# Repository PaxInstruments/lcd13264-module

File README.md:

# Pax Instruments
# LCD13264-module

[Pax Instruments Template Module](<link to store page>)

## Overview
The Pax Instruments LCD13264-module is a breakout shield for the LCD23164 graphic LCD.

## Repository Contents
- __Datasheets__ - Datasheets for relevant components and parts
- __Electronics__ - All PCB and schematic design files
- __Enclosure__ - Enclosure 3D design files
- __Firmware__ - Firmware, libraries, and examples
- __Production__ - Manufacturing resources
- __Resources__ - Other resources

## Product Versions

## License Information
```
Place the license statement here
```

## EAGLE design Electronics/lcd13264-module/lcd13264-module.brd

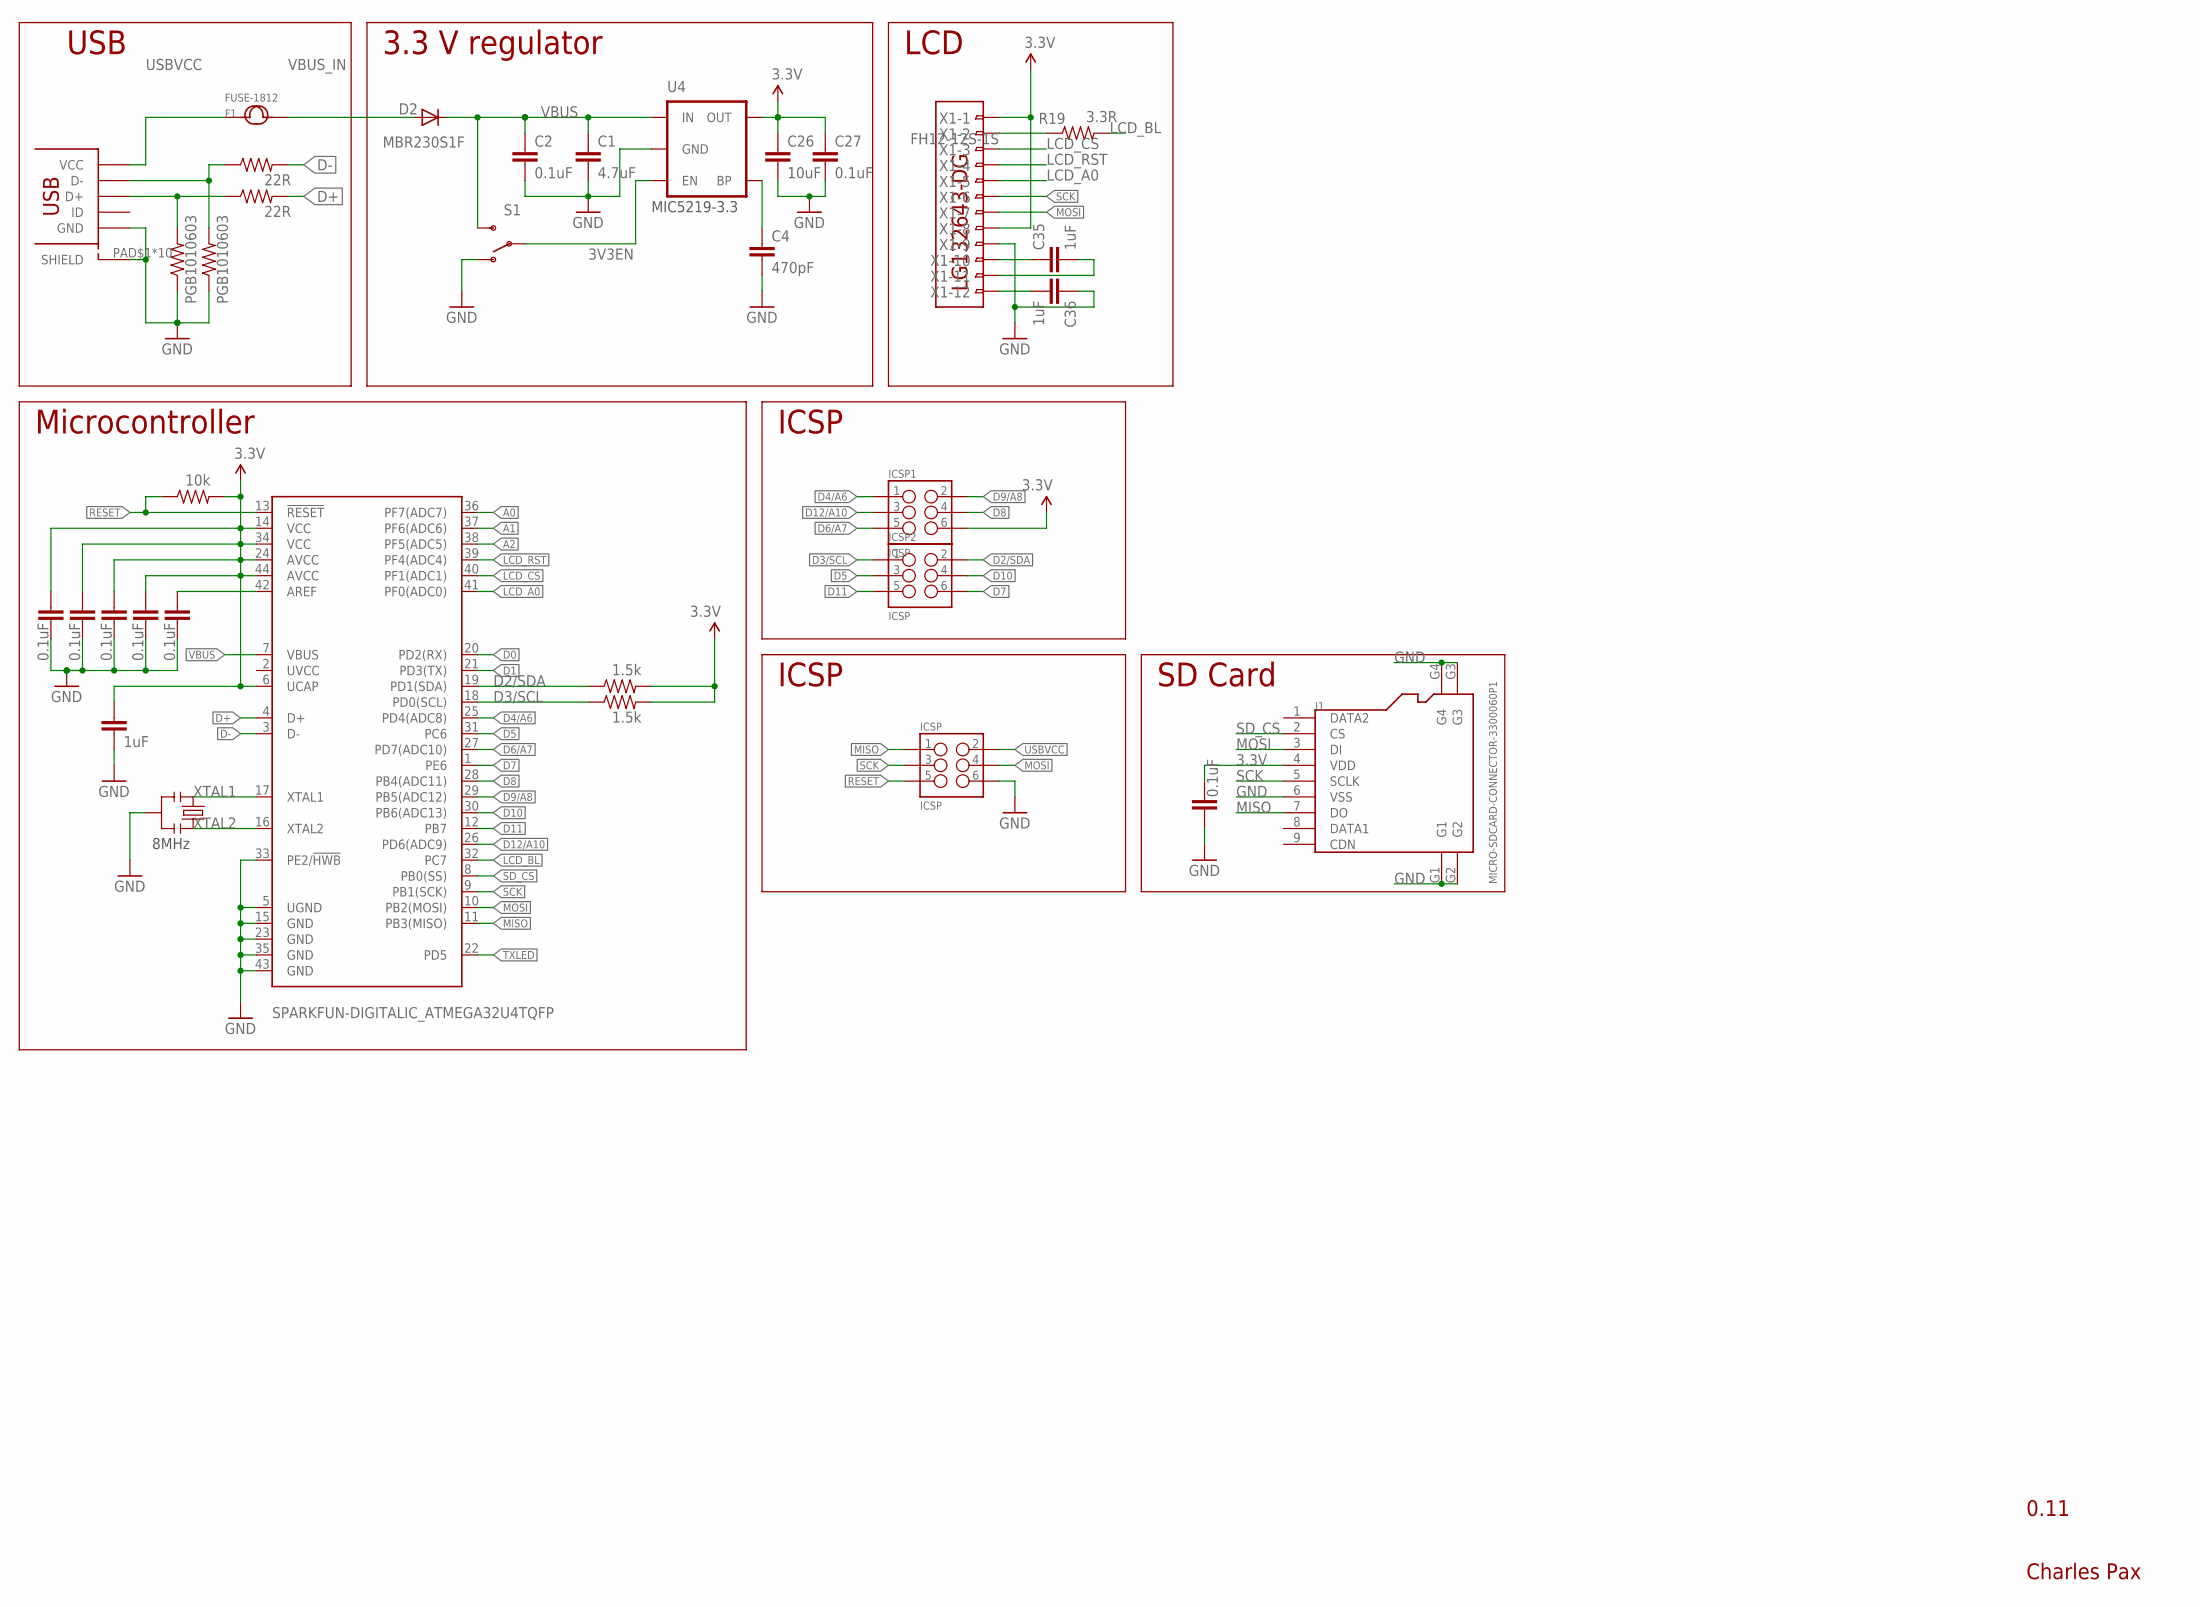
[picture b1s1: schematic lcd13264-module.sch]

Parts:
C1: 4.7uF; SPARKFUN-CAPACITORS_0603-CAP; MPN GRM188R60J475KE19D
C2, C3, C5, C21, C27, C32, C33, C34: 0.1uF; SPARKFUN-CAPACITORS_0603-CAP; MPN CL10B104KO8NNNC
C4: 470pF; SPARKFUN-CAPACITORS_0603-CAP; MPN C1608X5R1A474K080AA
C19, C35, C36: 1uF; SPARKFUN-CAPACITORS_0603-CAP; MPN LMK107B7105KA-T
C26: 10uF; SPARKFUN-CAPACITORS_0603-CAP; MPN JMK107ABJ106MAHT
D2: MBR230S1F; SOD123; MPN B340A-13-F
F1: FUSE-1812; F1812
ICSP, ICSP1, ICSP2: ICSP; SPARKFUN-CONNECTORS_2X3_SMT_POSTS_PAXINSTRUMENT; MPN 95278-101A06LF
J1: MICRO-SDCARD-CONNECTOR-3300060P1; 9P-SMD-W-RING
R4: 10k; SPARKFUN-RESISTORS_0603-RES; MPN RC1608J103CS
R9, R10: 22R; SPARKFUN-RESISTORS_0603-RES; MPN RC0603JR-0722RL
R13, R14: 1.5k; SPARKFUN-RESISTORS_0603-RES; MPN RC0603JR-071K5L
R19: 3.3R; SPARKFUN-RESISTORS_0603-RES
S1: SWITCH-SPDT-SMD-A; SWITCH-SPST-SMD-A
U4: MIC5219-3.3V; SOT23-5; MPN MIC5219-3.3YM5 TR
U$1: USB_MICROSMT+THRUHULE; USB_MICRO_THRUHOLE; MPN 10118194-0001LF
U$3: SPARKFUN-DIGITALIC_ATMEGA32U4TQFP; SPARKFUN-DIGITALIC_SPARKFUN-DIGITALIC_TQFP44
U$5: LG132643-DG; MPN LG132643-DW
X1: FH12-12S-1S; FH12-12S-1SH
Y1: RESONATORSMD; RESONATOR-SMD; MPN CSTCE8M00G52-R0
Z1, Z2: PGB1010603; SPARKFUN-RESISTORS_0603-RES; MPN PGB1010603NRHF

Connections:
3.3V: C5.1, C19.1, C21.2, C26.1, C27.1, C32.1, C33.1, C34.1, ICSP1.6, J1.4 (VDD), R4.2, R13.2, R14.2, U4.5 (OUT), U$3.6 (UCAP), U$3.14 (VCC), U$3.24 (AVCC), U$3.34 (VCC), U$3.44 (AVCC), X1.1, X1.8
3V3EN: S1.2, U4.3 (EN)
A0: U$3.36 (PF7(ADC7))
A1: U$3.37 (PF6(ADC6))
A2: U$3.38 (PF5(ADC5))
D0: U$3.20 (PD2(RX))
D1: U$3.21 (PD3(TX))
D2/SDA: ICSP2.2, R13.1, U$3.19 (PD1(SDA))
D3/SCL: ICSP2.1, R14.1, U$3.18 (PD0(SCL))
D4/A6: ICSP1.1, U$3.25 (PD4(ADC8))
D5: ICSP2.3, U$3.31 (PC6)
D6/A7: ICSP1.5, U$3.27 (PD7(ADC10))
D7: ICSP2.6, U$3.1 (PE6)
D8: ICSP1.4, U$3.28 (PB4(ADC11))
D9/A8: ICSP1.2, U$3.29 (PB5(ADC12))
D10: ICSP2.4, U$3.30 (PB6(ADC13))
D11: ICSP2.5, U$3.12 (PB7)
D12/A10: ICSP1.3, U$3.26 (PD6(ADC9))
D+: R9.2, U$3.4 (D+)
D-: R10.2, U$3.3 (D-)
GND: C1.2, C2.2, C3.2, C4.2, C5.2, C19.2, C21.1, C26.2, C27.2, C32.2, C33.2, C34.2, C36.1, ICSP.6, J1.6 (VSS), J1.G1, J1.G2, J1.G3, J1.G4, S1.1 (O), U4.2 (GND), U$1.PAD$1 (SHIELD), U$1.PAD$2 (SHIELD), U$1.PAD$3 (SHIELD), U$1.PAD$4 (SHIELD), U$1.PAD$5 (SHIELD), U$1.PAD$6 (SHIELD), U$1.PAD$7 (SHIELD), U$1.PAD$8 (SHIELD), U$1.PAD$9 (SHIELD), U$1.PAD$10 (SHIELD), U$1.PIN$5 (GND), U$3.5 (UGND), U$3.15 (GND), U$3.23 (GND), U$3.33 (PE2/!HWB), U$3.35 (GND), U$3.43 (GND), X1.9, Y1.2, Z1.1, Z2.1
LCD_A0: U$3.41 (PF0(ADC0)), X1.5
LCD_BL: R19.2, U$3.32 (PC7)
LCD_CS: U$3.40 (PF1(ADC1)), X1.3
LCD_RST: U$3.39 (PF4(ADC4)), X1.4
MISO: ICSP.1, J1.7 (DO), U$3.11 (PB3(MISO))
MOSI: ICSP.4, J1.3 (DI), U$3.10 (PB2(MOSI)), X1.7
unnamed: C4.1, U4.4 (BP)
unnamed: R19.1, X1.2
unnamed: C35.1, X1.10
unnamed: C36.2, X1.12
unnamed: C3.1, U$3.42 (AREF)
unnamed: R10.1, U$1.PIN$2 (D-), Z2.2
unnamed: R9.1, U$1.PIN$3 (D+), Z1.2
unnamed: C35.2, X1.11
RESET: ICSP.5, R4.1, U$3.13 (!RESET)
SCK: ICSP.3, J1.5 (SCLK), U$3.9 (PB1(SCK)), X1.6
SD_CS: J1.2 (CS), U$3.8 (PB0(SS))
TXLED: U$3.22 (PD5)
USBVCC: F1.1, ICSP.2, U$1.PIN$1 (VCC)
VBUS: C1.1, C2.1, D2.C, S1.3 (S), U4.1 (IN), U$3.7 (VBUS)
VBUS_IN: D2.A, F1.2
XTAL1: U$3.17 (XTAL1), Y1.1
XTAL2: U$3.16 (XTAL2), Y1.3

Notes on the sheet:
MIC5219-3.3
8MHz
USB
3.3 V regulator
LCD
Microcontroller
ICSP
0.11
Charles Pax
SD Card

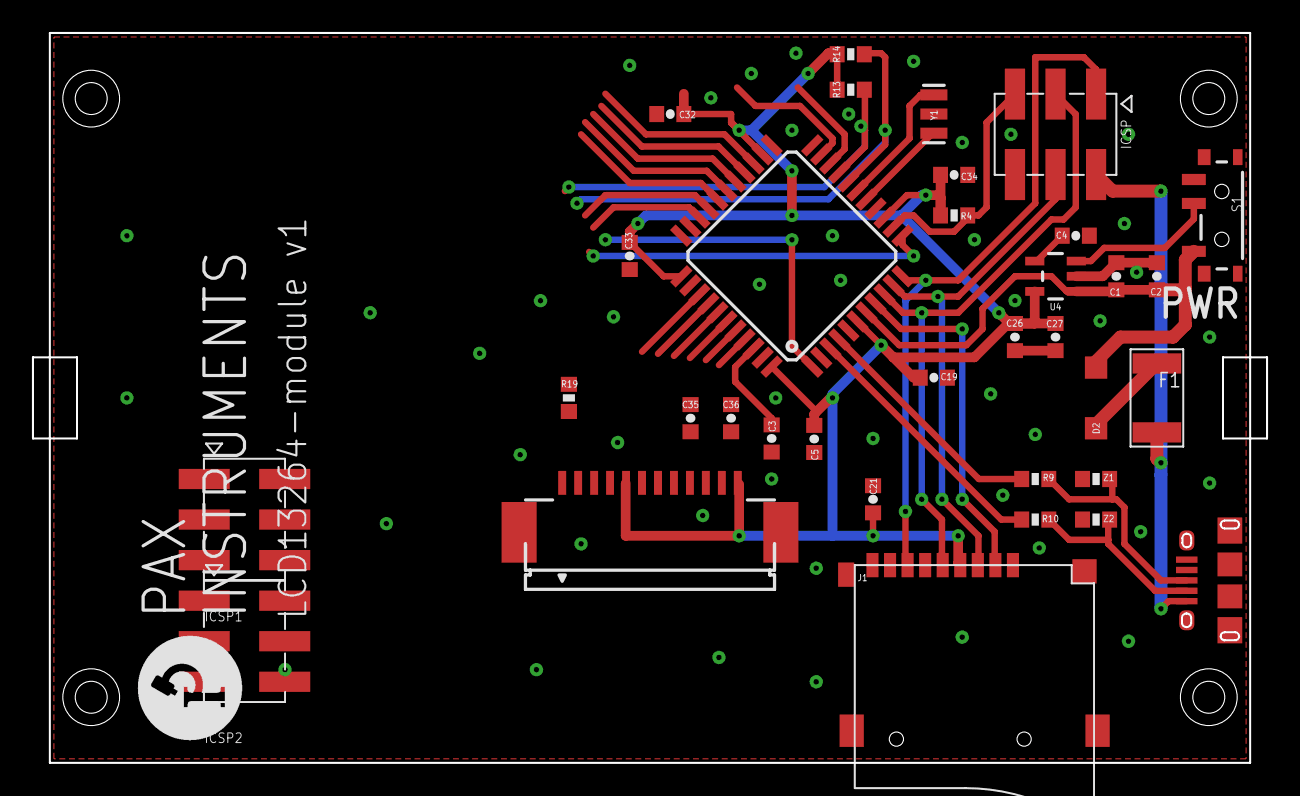
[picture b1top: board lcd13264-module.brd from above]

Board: 2 copper layers, 77.3 x 45.7 mm, 36 parts (0 on the bottom side), 38 nets.

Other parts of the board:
U$6: PAXINSTRUMENT_LOGO

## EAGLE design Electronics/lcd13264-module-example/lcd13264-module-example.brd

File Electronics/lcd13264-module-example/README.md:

# Pax Instruments
# LCD13264-module

Developed by <person(s) name> for [Pax Instruments](http://paxinstruments.com/), an original design.

## Overview
This is the electronics for the Pax Instruments LCD13264-module designed in Cadsoft Eagle.

## License
```
Place the license statement here
```

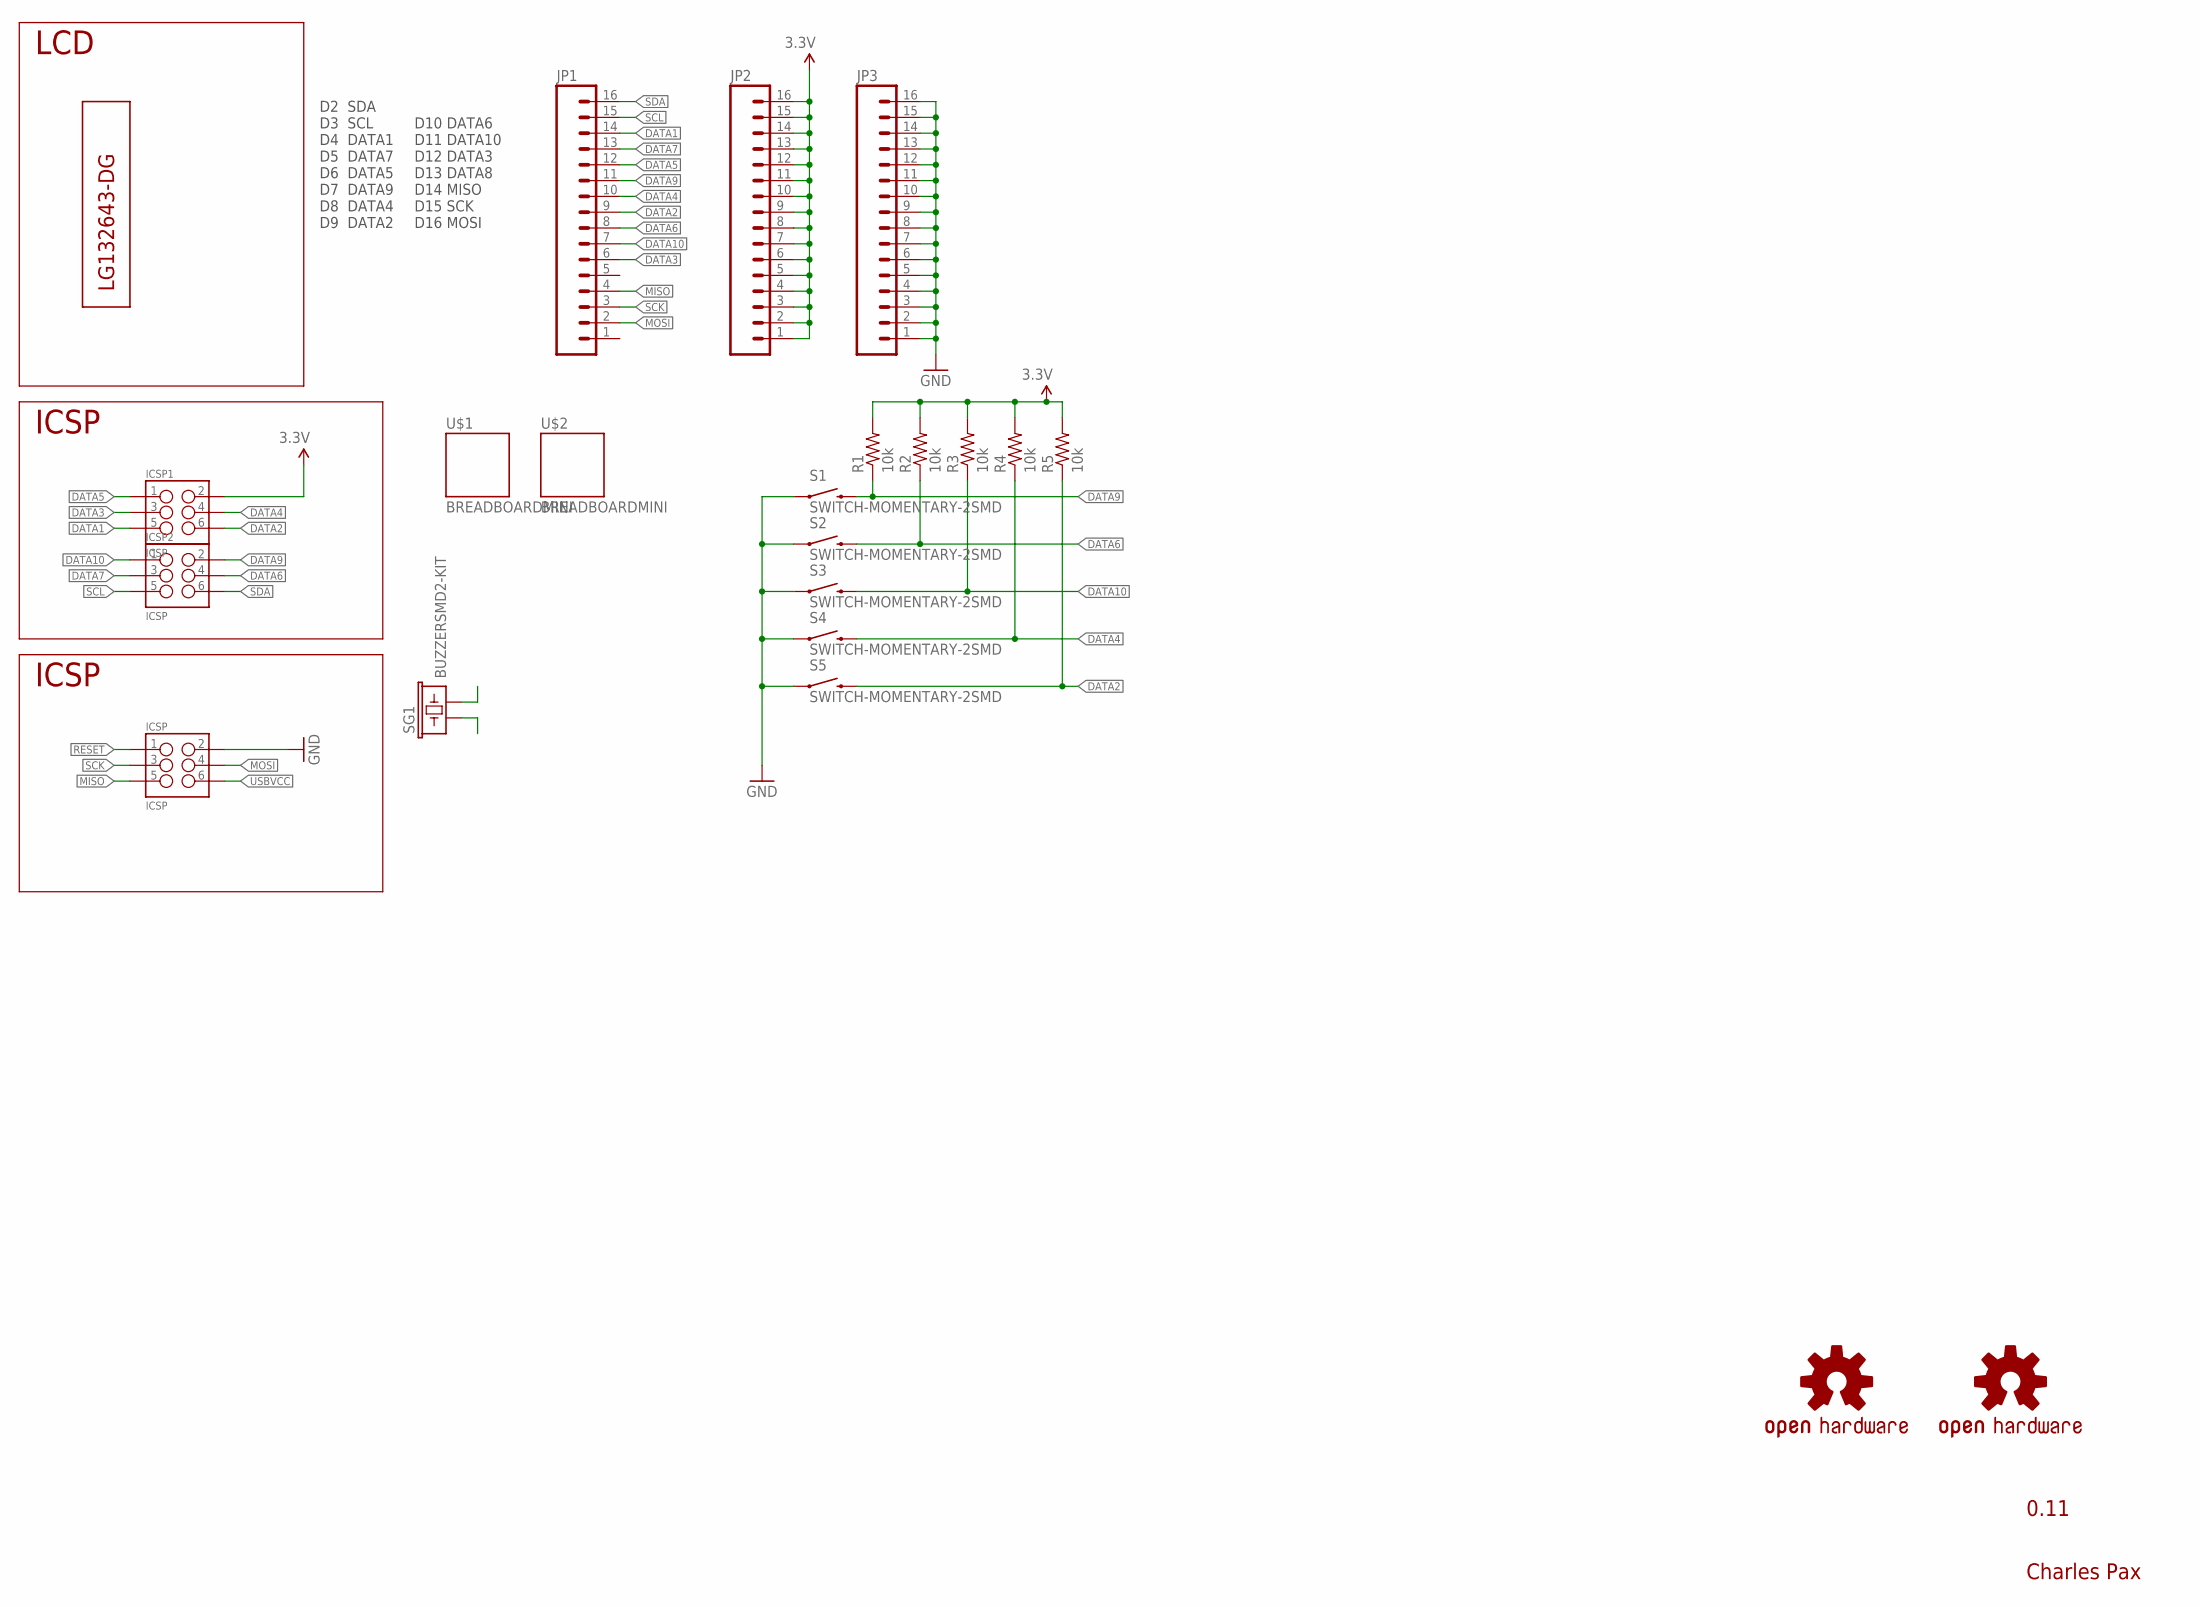
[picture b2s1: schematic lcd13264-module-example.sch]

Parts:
ICSP, ICSP1, ICSP2: ICSP; SPARKFUN-CONNECTORS_2X3_SMT_POSTS_PAXINSTRUMENT; MPN 95278-101A06LF
JP1, JP2, JP3: M161X16_NO_SILK; 1X16_NO_SILK
LOGO1: OSHW-LOGOL; OSHW-LOGO-L
LOGO2: OSHW-LOGOL-COPPER; OSHW-LOGO-L_COPPER
R1, R2, R3, R4, R5: 10k; 0603-RES
S1, S2, S3, S4, S5: SWITCH-MOMENTARY-2SMD; TACTILE-SWITCH-SMD
SG1: BUZZERSMD2-KIT; BUZZER-CCV-KIT
U$1, U$2: BREADBOARDMINI; BREADBOARD-MINI
U$5: LG132643-DG; MPN LG132643-DW

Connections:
3.3V: ICSP1.2, JP2.1, JP2.2, JP2.3, JP2.4, JP2.5, JP2.6, JP2.7, JP2.8, JP2.9, JP2.10, JP2.11, JP2.12, JP2.13, JP2.14, JP2.15, JP2.16, R1.2, R2.2, R3.2, R4.2, R5.2
DATA1: ICSP1.5, JP1.14
DATA2: ICSP1.6, JP1.9, R5.1, S5.3 (2)
DATA3: ICSP1.3, JP1.6
DATA4: ICSP1.4, JP1.10, R4.1, S4.3 (2)
DATA5: ICSP1.1, JP1.12
DATA6: ICSP2.4, JP1.8, R2.1, S2.3 (2)
DATA7: ICSP2.3, JP1.13
DATA9: ICSP2.2, JP1.11, R1.1, S1.3 (2)
DATA10: ICSP2.1, JP1.7, R3.1, S3.3 (2)
GND: ICSP.2, JP3.1, JP3.2, JP3.3, JP3.4, JP3.5, JP3.6, JP3.7, JP3.8, JP3.9, JP3.10, JP3.11, JP3.12, JP3.13, JP3.14, JP3.15, JP3.16, S1.1, S2.1, S3.1, S4.1, S5.1
MISO: ICSP.5, JP1.4
MOSI: ICSP.4, JP1.2
RESET: ICSP.1
SCK: ICSP.3, JP1.3
SCL: ICSP2.5, JP1.15
SDA: ICSP2.6, JP1.16
USBVCC: ICSP.6

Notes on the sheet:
LCD
ICSP
0.11
Charles Pax
D2 SDA D3 SCL D4 DATA1 D5 DATA7 D6 DATA5 D7 DATA9 D8 DATA4 D9 DATA2
D10 DATA6 D11 DATA10 D12 DATA3 D13 DATA8 D14 MISO D15 SCK D16 MOSI

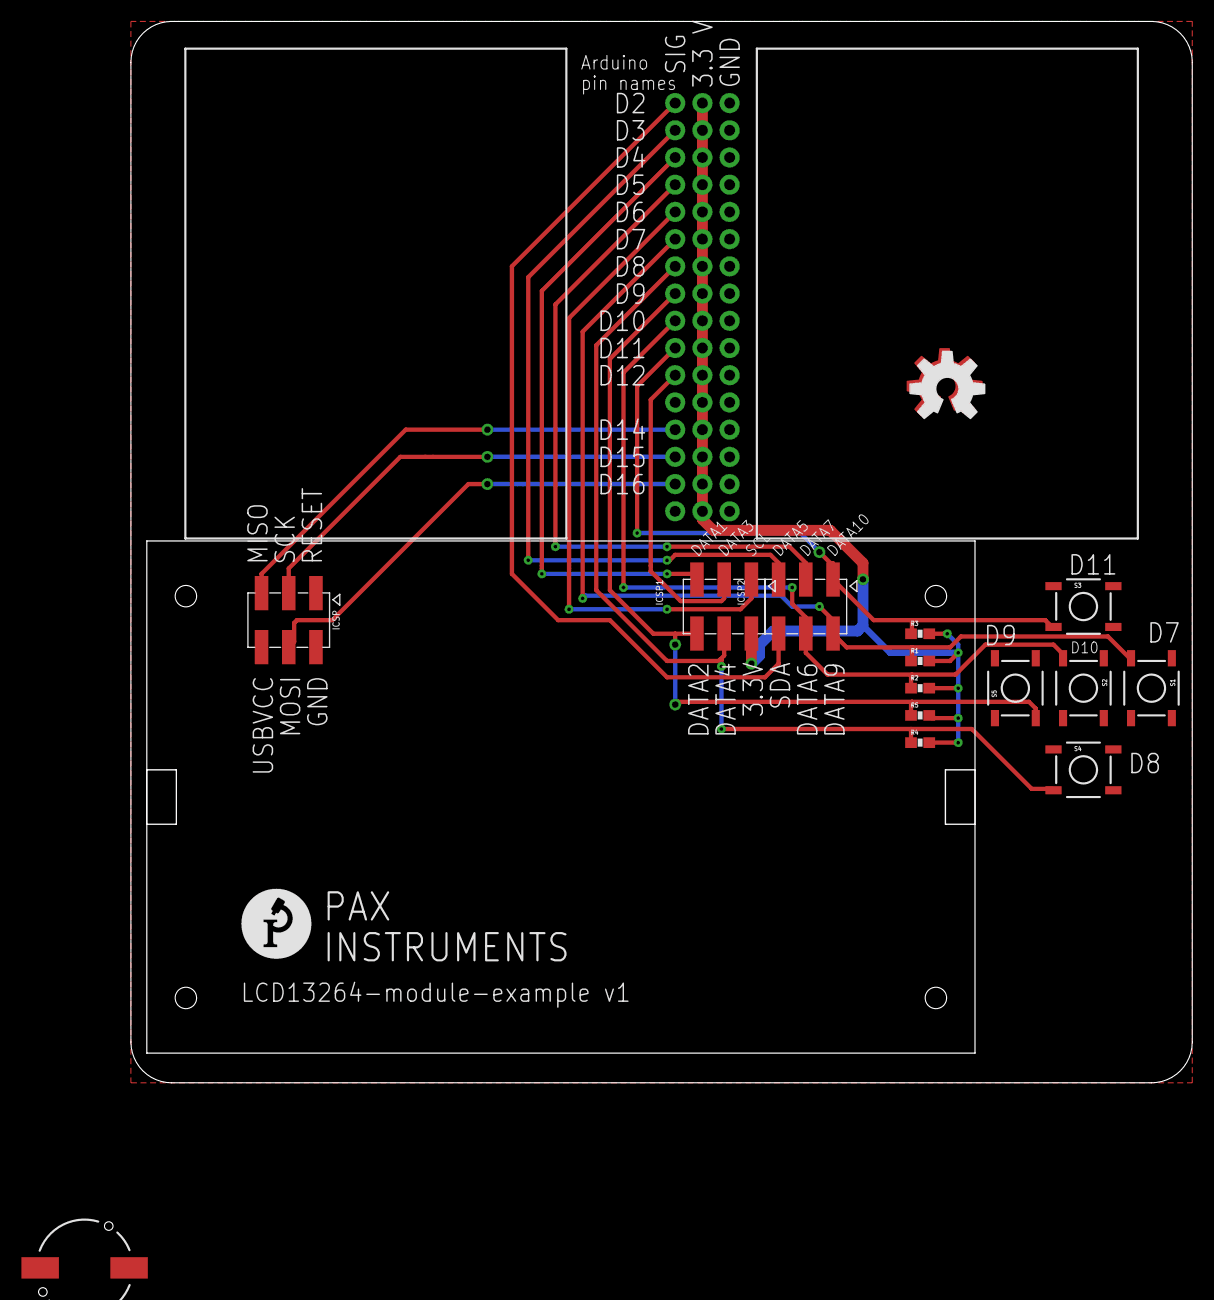
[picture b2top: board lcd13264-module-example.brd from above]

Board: 2 copper layers, 99.1 x 99.1 mm, 23 parts (1 on the bottom side), 16 nets.

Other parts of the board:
U$6: PAXINSTRUMENT_LOGO

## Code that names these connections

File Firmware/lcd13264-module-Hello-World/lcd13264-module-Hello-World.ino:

/*

  HelloWorld.pde
  
  "Hello World!" example code.
  
  >>> Before compiling: Please remove comment from the constructor of the 
  >>> connected graphics display (see below).
  
  Universal 8bit Graphics Library, http://code.google.com/p/u8glib/
  
  Copyright (c) 2012, olikraus@gmail.com
  All rights reserved.

  Redistribution and use in source and binary forms, with or without modification, 
  are permitted provided that the following conditions are met:

  * Redistributions of source code must retain the above copyright notice, this list 
    of conditions and the following disclaimer.
    
  * Redistributions in binary form must reproduce the above copyright notice, this 
    list of conditions and the following disclaimer in the documentation and/or other 
    materials provided with the distribution.

  THIS SOFTWARE IS PROVIDED BY THE COPYRIGHT HOLDERS AND 
  CONTRIBUTORS "AS IS" AND ANY EXPRESS OR IMPLIED WARRANTIES, 
  INCLUDING, BUT NOT LIMITED TO, THE IMPLIED WARRANTIES OF 
  MERCHANTABILITY AND FITNESS FOR A PARTICULAR PURPOSE ARE 
  DISCLAIMED. IN NO EVENT SHALL THE COPYRIGHT HOLDER OR 
  CONTRIBUTORS BE LIABLE FOR ANY DIRECT, INDIRECT, INCIDENTAL, 
  SPECIAL, EXEMPLARY, OR CONSEQUENTIAL DAMAGES (INCLUDING, BUT 
  NOT LIMITED TO, PROCUREMENT OF SUBSTITUTE GOODS OR SERVICES; 
  LOSS OF USE, DATA, OR PROFITS; OR BUSINESS INTERRUPTION) HOWEVER 
  CAUSED AND ON ANY THEORY OF LIABILITY, WHETHER IN CONTRACT, 
  STRICT LIABILITY, OR TORT (INCLUDING NEGLIGENCE OR OTHERWISE) 
  ARISING IN ANY WAY OUT OF THE USE OF THIS SOFTWARE, EVEN IF 
  ADVISED OF THE POSSIBILITY OF SUCH DAMAGE.  
  
*/

// This documen is modified to work with the Pax Instruments LCD Test Board v0.2
#define LCD_MOSI             A0
#define LCD_SCK              A1
#define LCD_A0               A2
#define LCD_RST              A3
#define LCD_CS               A4
#define LCD_BACKLIGHT_PIN    A5    // LCD backlight on pin
// MISO                     14
// SCK                      15
// MOSI                     16
#define SW_A_pin             11
#define SW_B_pin             9
#define SW_C_pin             10
#define SW_D_pin             7
#define SW_E_pin             8
#define SD_CS                17

#define LCD_CONTRAST     0x018*7  // Sets the LCD contrast

#include "U8glib.h"
#include <SdFat.h>

// U8GLIB_PI13264  u8g(LCD_CS, LCD_A0, LCD_RST); // Use HW-SPI
 U8GLIB_PI13264  u8g(LCD_SCK, LCD_MOSI, LCD_CS, LCD_A0, LCD_RST); // Use SW-SPI

SdFat sd;
SdFile myFile;
int sd_test_status = 0;

int SW_A_state = 0;
int SW_B_state = 0;
int SW_C_state = 0;
int SW_D_state = 0;
int SW_E_state = 0;

int fadeValue = 0;
int updown = 1; // is the fading going up or down

int sdTest(){
//  Serial.begin(9600);
//  while (!Serial) {}  // wait for Leonardo
//  Serial.println("Type any character to start");
//  while (Serial.read() <= 0) {}
//  delay(400);  // catch Due reset problem
 // if (sd.begin(SD_CS, SPI_HALF_SPEED)) sd.initErrorHalt();
  sd.begin(SD_CS, SPI_HALF_SPEED);
  if (!myFile.open("test.txt", O_RDWR | O_CREAT | O_AT_END)) {
    //sd.errorHalt("opening test.txt for write failed");
    return 0;
  }
//  Serial.print("Writing to test.txt...");
  myFile.println("testing 1, 2, 3.");
  myFile.close();
//  Serial.println("done.");
  if (!myFile.open("test.txt", O_READ)) {
   // sd.errorHalt("opening test.txt for read failed");
    return 0;
  }
//  Serial.println("test.txt:");
  int data;
  while ((data = myFile.read()) >= 0) Serial.write(data);
  // close the file:
  myFile.close();
  return 1;
}

void draw(void) {
  // graphic commands to redraw the complete screen should be placed here  
  //u8g.setFont(u8g_font_unifont);
  u8g.setFont(u8g_font_ncenR12);
  u8g.drawStr( 0, 14, "PAX");
  u8g.drawStr( 0, 30, "INSTRUMENTS");
  
  u8g.setFont(u8g_font_5x8);
  u8g.drawStr( 0, 39, "OPENSOURCE LAB INSTRUMENTS");
  u8g.drawStr( 0, 62, "Graphic LCD 132x64 shield");
  
  // Draw button stuff
  if (SW_A_state == LOW) {     
    u8g.drawStr( 0, 50, "A");
  } 
  if (SW_B_state == LOW) {     
    u8g.drawStr( 5, 50, "B");
  } 
  if (SW_C_state == LOW) {     
    u8g.drawStr( 10, 50, "C");
  } 
  if (SW_D_state == LOW) {     
    u8g.drawStr( 15, 50, "D");
    if (SW_C_state == LOW){
      if (sd_test_status == 0){
        u8g.drawStr( 75, 50, "SD: bad");
      }
      if (sd_test_status == 1){
        u8g.drawStr( 75, 50, "SD: okay");
      }
    }
  } 
  if (SW_E_state == LOW) {     
    u8g.drawStr( 20, 50, "E  Fading...");
  } 
}

void setup(void) {
  sd_test_status = sdTest();
    // flip screen, if required
  u8g.setRot180();
  u8g.setContrast(LCD_CONTRAST);
  
  pinMode(LCD_BACKLIGHT_PIN, OUTPUT);           
  analogWrite(LCD_BACKLIGHT_PIN, fadeValue);   

  // assign default color value
  if ( u8g.getMode() == U8G_MODE_R3G3B2 ) {
    u8g.setColorIndex(255);     // white
  }
  else if ( u8g.getMode() == U8G_MODE_GRAY2BIT ) {
    u8g.setColorIndex(3);         // max intensity
  }
  else if ( u8g.getMode() == U8G_MODE_BW ) {
    u8g.setColorIndex(1);         // pixel on
  }
  else if ( u8g.getMode() == U8G_MODE_HICOLOR ) {
    u8g.setHiColorByRGB(255,255,255);
  }
  
  // Set up the buttons
    pinMode(SW_A_pin, INPUT);
    pinMode(SW_B_pin, INPUT);
    pinMode(SW_C_pin, INPUT);
    pinMode(SW_D_pin, INPUT);
    pinMode(SW_E_pin, INPUT);
}



void loop(void) {
  SW_A_state = digitalRead(SW_A_pin);
  SW_B_state = digitalRead(SW_B_pin);
  SW_C_state = digitalRead(SW_C_pin);
  SW_D_state = digitalRead(SW_D_pin);
  SW_E_state = digitalRead(SW_E_pin);
  
  // picture loop
  u8g.firstPage();  
  do {
    draw();
  } while( u8g.nextPage() );
  // rebuild the picture after some delay
  delay(50);
  
  // fade in from min to max in increments of 5 points:

  while(SW_E_state == false){
    if (fadeValue >=255){
      updown = 0;
    }
    if (fadeValue <= 0 ){
      updown = 1;
    }
    
    analogWrite(LCD_BACKLIGHT_PIN, fadeValue);         
    delay(10);
    if (updown == true){
      fadeValue +=5;
    }
    if (updown == false){
      fadeValue -=5;
    }
    SW_E_state = digitalRead(SW_E_pin);
  }
  if (SW_D_state == false){
   sd_test_status = sdTest(); 
  }
}

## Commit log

2015-04-17 Added PCD design. Just need to breakout some data pins now.
2015-04-18 Finished layout of v1. Copied design to v1 folder. Sending to board house.
2015-04-18 Added a template daughter board outline 10 x 10 cm.\n- verified the pins match between the two boards.
2015-04-18 Added an example board using the LCD module template. Just headers, a buzzer, breadboards, and buttons.
2015-04-18 Sending module example to board house. Added a module example versions volder.
2015-04-18 Updated LCD connector.
2015-04-22 Aremoved template module.
2015-04-22 Added a Hellow, World program.
2016-04-30 Unknown changes.

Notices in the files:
parts and their libraries:
SparkFun-Connectors: Licensing: Creative Commons ShareAlike 4.0 International - https://creativecommons.org/licenses/by-sa/4.0
SparkFun-Aesthetics: Licensing: CC v3.0 Share-Alike You are welcome to use this library for commercial purposes.
